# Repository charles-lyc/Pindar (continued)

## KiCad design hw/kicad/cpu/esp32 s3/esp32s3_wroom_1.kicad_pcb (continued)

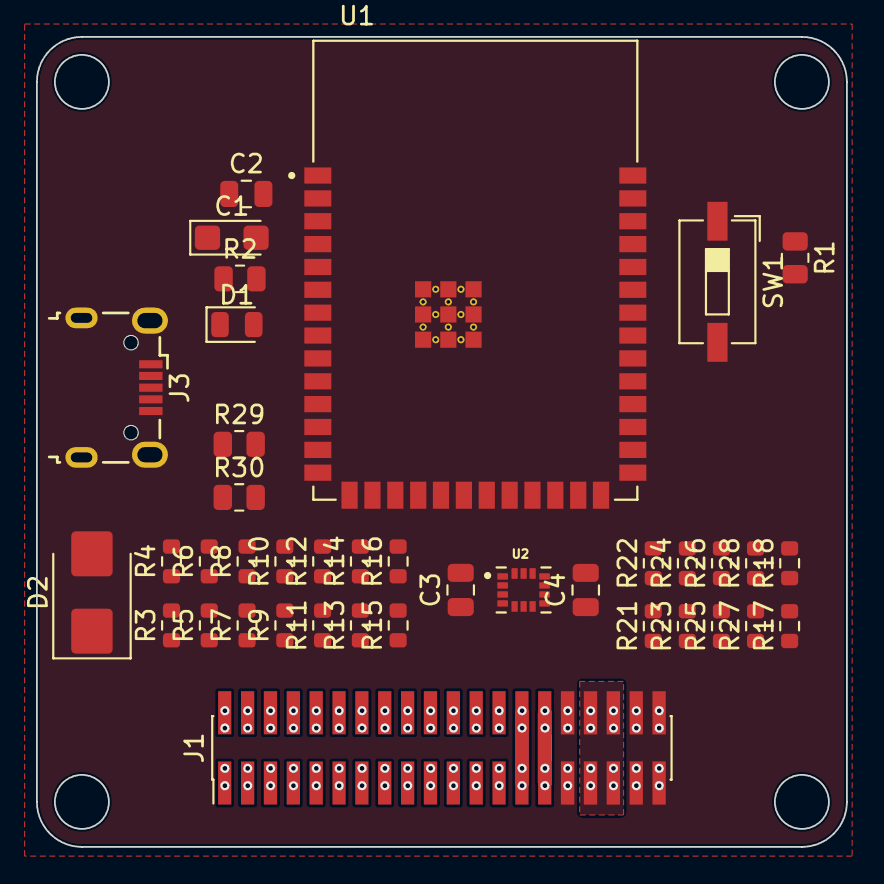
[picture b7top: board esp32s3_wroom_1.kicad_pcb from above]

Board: 2 copper layers, 45.0 x 45.0 mm, 40 parts (1 on the bottom side), 61 nets.

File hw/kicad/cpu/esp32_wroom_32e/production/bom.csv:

Designator,Footprint,Quantity,Value,LCSC Part #
C1,CP_EIA-7343-20_Kemet-V,1,200uF,
"C2, C3, C4",0603,3,0.1uF,
"J1, J2",PinHeader_2x20_P1.27mm_Vertical_SMD,2,Conn_02x20_Odd_Even,
"R1, R12, R13, R14, R15, R16, R17, R19, R2, R20, R21, R22, R23, R24, R25, R3, R4, R5, R6, R9",0603,20,100,
"R7, R8",0603,2,2k,
U1,ESP32-WROOM-32,1,ESP32-WROOM-32,
U2,ICM-42688-P,1,ICM-42688-P,

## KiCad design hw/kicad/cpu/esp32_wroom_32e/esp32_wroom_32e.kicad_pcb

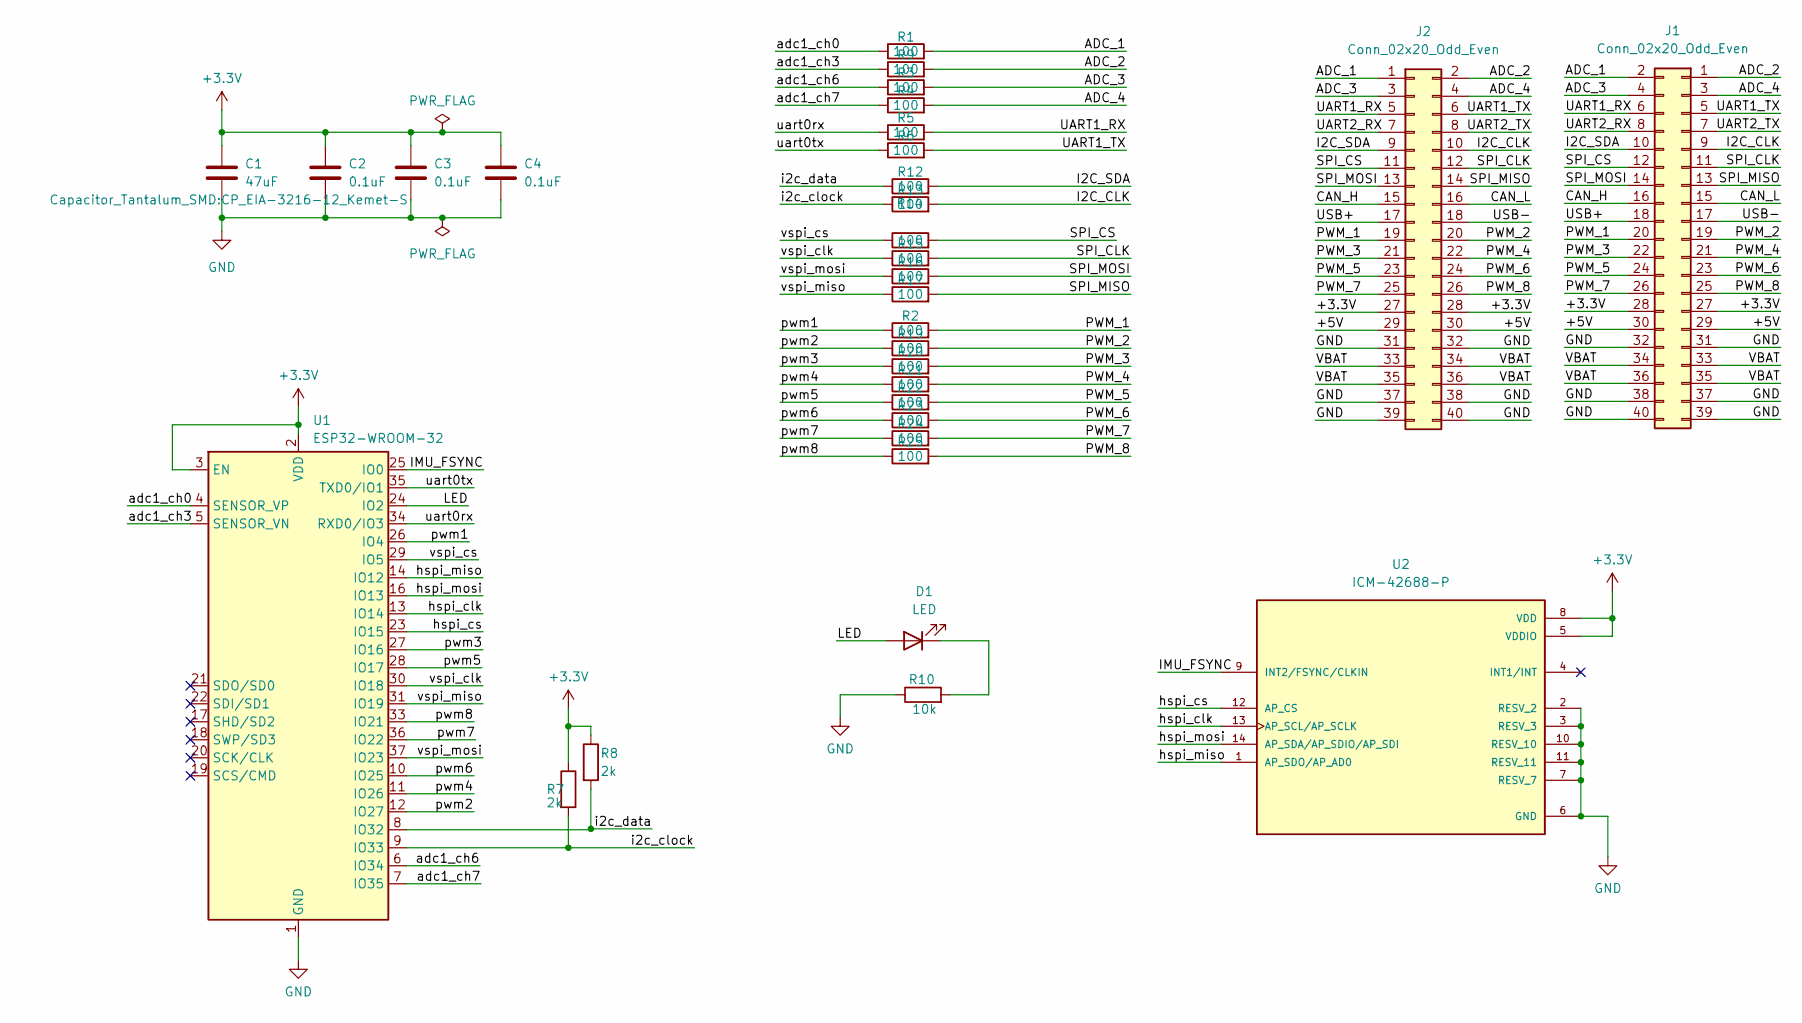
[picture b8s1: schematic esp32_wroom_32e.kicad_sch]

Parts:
C1: 47uF; CP_EIA-3216-12_Kemet-S
C2, C3, C4: 0.1uF; C_0805_2012Metric
D1: LED; LED_0805_2012Metric
J1, J2: Conn_02x20_Odd_Even; PinHeader_2x20_P1.27mm_Vertical_SMD
R1, R2, R3, R4, R5, R6, R9, R12, R13, R14, R15, R16, R17, R19, R20, R21, R22, R23, R24, R25: 100; R_0603_1608Metric
R7, R8: 2k; R_0805_2012Metric
R10: 10k; R_0805_2012Metric
U1: ESP32-WROOM-32
U2: ICM-42688-P; PARTREV 1.2

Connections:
+3.3V: C1.1, C2.1, C3.1, C4.1, J1.27, J1.28, J2.27, J2.28, R7.1, R8.1, U1.2 (VDD), U1.3 (EN), U2.5 (VDDIO), U2.8 (VDD)
/+5V: J1.29, J1.30, J2.29, J2.30
/ADC_1: J1.2, J2.1, R1.2
/ADC_2: J1.1, J2.2, R9.2
/ADC_3: J1.4, J2.3, R3.2
/ADC_4: J1.3, J2.4, R4.2
/CAN_H: J1.16, J2.15
/CAN_L: J1.15, J2.16
/I2C_CLK: J1.9, J2.10, R13.2
/I2C_SDA: J1.10, J2.9, R12.2
/IMU_FSYNC: U1.25 (IO0), U2.9 (INT2/FSYNC/CLKIN)
/LED: D1.2 (A), U1.24 (IO2)
/PWM_1: J1.20, J2.19, R2.2
/PWM_2: J1.19, J2.20, R19.2
/PWM_3: J1.22, J2.21, R20.2
/PWM_4: J1.21, J2.22, R21.2
/PWM_5: J1.24, J2.23, R22.2
/PWM_6: J1.23, J2.24, R23.2
/PWM_7: J1.26, J2.25, R24.2
/PWM_8: J1.25, J2.26, R25.2
/SPI_CLK: J1.11, J2.12, R15.2
/SPI_CS: J1.12, J2.11, R14.2
/SPI_MISO: J1.13, J2.14, R17.2
/SPI_MOSI: J1.14, J2.13, R16.2
/UART1_RX: J1.6, J2.5, R5.2
/UART1_TX: J1.5, J2.6, R6.2
/UART2_RX: J1.8, J2.7
/UART2_TX: J1.7, J2.8
/USB+: J1.18, J2.17
/USB-: J1.17, J2.18
/VBAT: J1.33, J1.34, J1.35, J1.36, J2.33, J2.34, J2.35, J2.36
/adc1_ch0: R1.1, U1.4 (SENSOR_VP)
/adc1_ch3: R9.1, U1.5 (SENSOR_VN)
/adc1_ch6: R3.1, U1.6 (IO34)
/adc1_ch7: R4.1, U1.7 (IO35)
/hspi_clk: U1.13 (IO14), U2.13 (AP_SCL/AP_SCLK)
/hspi_cs: U1.23 (IO15), U2.12 (AP_CS)
/hspi_miso: U1.14 (IO12), U2.1 (AP_SDO/AP_AD0)
/hspi_mosi: U1.16 (IO13), U2.14 (AP_SDA/AP_SDIO/AP_SDI)
/i2c_clock: R7.2, R13.1, U1.9 (IO33)
/i2c_data: R8.2, R12.1, U1.8 (IO32)
/pwm1: R2.1, U1.26 (IO4)
/pwm2: R19.1, U1.12 (IO27)
/pwm3: R20.1, U1.27 (IO16)
/pwm4: R21.1, U1.11 (IO26)
/pwm5: R22.1, U1.28 (IO17)
/pwm6: R23.1, U1.10 (IO25)
/pwm7: R24.1, U1.36 (IO22)
/pwm8: R25.1, U1.33 (IO21)
/uart0rx: R5.1, U1.34 (RXD0/IO3)
/uart0tx: R6.1, U1.35 (TXD0/IO1)
/vspi_clk: R15.1, U1.30 (IO18)
/vspi_cs: R14.1, U1.29 (IO5)
/vspi_miso: R17.1, U1.31 (IO19)
/vspi_mosi: R16.1, U1.37 (IO23)
GND: C1.2, C2.2, C3.2, C4.2, J1.31, J1.32, J1.37, J1.38, J1.39, J1.40, J2.31, J2.32, J2.37, J2.38, J2.39, J2.40, R10.1, U1.1 (GND), U1.15 (GND), U1.38 (GND), U1.39 (GND), U2.2 (RESV_2), U2.3 (RESV_3), U2.6 (GND), U2.7 (RESV_7), U2.10 (RESV_10), U2.11 (RESV_11)
unnamed: D1.1 (K), R10.2

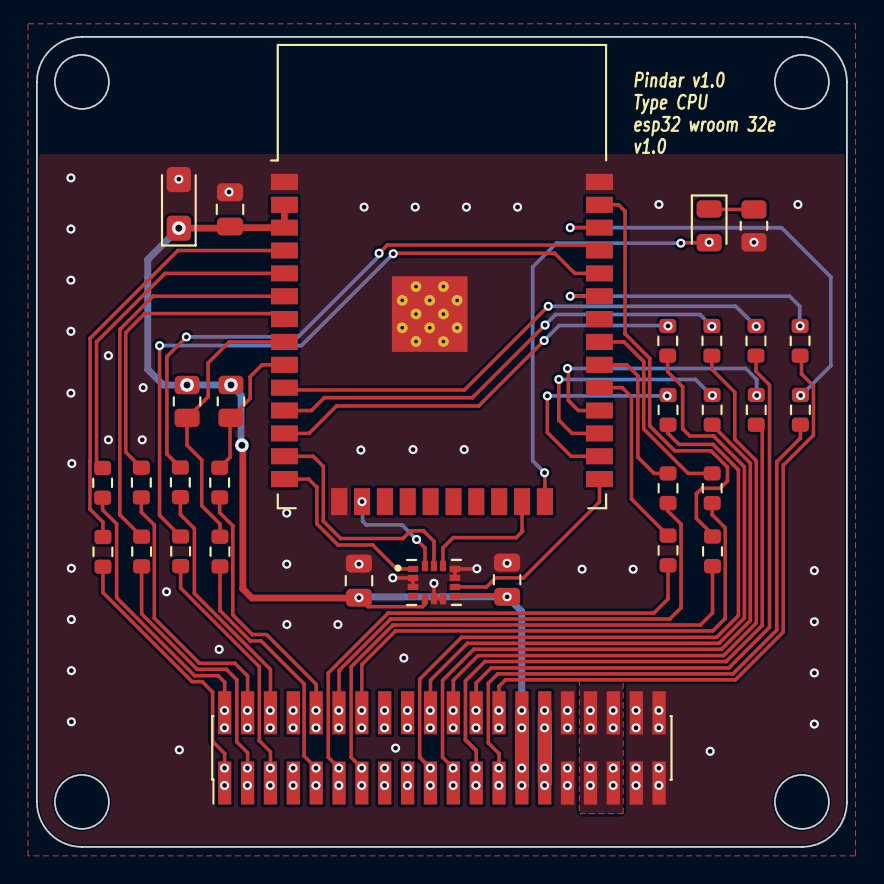
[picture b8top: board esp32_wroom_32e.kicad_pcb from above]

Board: 2 copper layers, 45.0 x 45.0 mm, 32 parts (1 on the bottom side), 57 nets.

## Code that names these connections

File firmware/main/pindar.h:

#pragma once

#include "freertos/FreeRTOS.h"
#include "freertos/task.h"
#include "freertos/semphr.h"

#include "mcu/spi.h"
#include "mcu/gpio_intr.h"

class Pindar {
public:
	// on board imu bus and gpio
	Pindar();
	~Pindar();

	// SerialPort *serial1= nullptr;
	// SerialPort *serial2= nullptr;

	SPI_Interface *spi2_bus = nullptr;
	SPI_Interface *spi3_bus = nullptr;
	// I2C_Interface *i2c_bus = nullptr;
	GPIO_Interrupt *gpio_imu = nullptr;

	// GPIO_Interface *gpio_1;
	// GPIO_Interface *gpio_2;
	// GPIO_Interface *gpio_3;
	// GPIO_Interface *gpio_4;
	// GPIO_Interface *gpio_5;
	// GPIO_Interface *gpio_6;
	// GPIO_Interface *gpio_7;
	// GPIO_Interface *gpio_8;
	// GPIO_Interface *gpio_9;
	// GPIO_Interface *gpio_10;
	// GPIO_Interface *gpio_11;
	// GPIO_Interface *gpio_12;
private:
};

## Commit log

2023-06-21 第一次打板，感觉可以再做小一点，并更新几个小问题。
2023-06-23 修改尺寸至45x45
2023-06-23 更新了template
2023-06-24 Pindar v1.0
2023-06-24 更新read me
2023-06-25 新增陀螺仪小板子
2023-06-29 第二次打样的整改；dc motor改成了三路 io不够做不了四路；
2023-06-29 修改名字
2023-06-30 更换接口线序
2023-07-01 更新app gyro板
2023-07-02 我又改接口了
2023-07-05 尽力改成40mmx40mm
2023-07-06 esp32部分该小板框可太难了，小电阻太多，只好全部去掉。
2023-07-06 原件位置
2023-07-08 cpu板io电阻
2023-07-08 增加电流传感器芯片
2023-07-13 更新dc motor板
2023-07-13 新增app板 PMW3360
2023-07-13 更新power16V板
2023-07-13 更新CPU板
2023-07-14 更新ESP32 S3 CPU板
2023-07-14 更新打样资料
2023-07-15 更新gyro
2023-07-23 更新power16v一些错误
2023-07-24 修改光流板一些错误
2023-07-30 更新USB micro 为优信的封装
2023-08-01 pindar平台接口的初步构想，但实际情况是，直接用esp32的API写几个器件驱动，后续照着这个模板来做即可，单独封一层显得多余。不过仍可以慢慢补充，当哪天接口覆盖面足够时就可以直接用pindar简化过的接口了。
2023-08-01 添加了io口定义，任何外设只要include了io定义+esp32的接口，就可以使用pindar bus上的资源了
2023-08-01 添加battery示例
2023-08-07 更新fw
2023-08-09 更新gitignore
2023-08-15 新增APP板 ADIS16460
2023-08-21 更新了代码框架
2023-08-22 更新IMU细节
2023-08-23 更新imu_scan_test
2023-08-23 fix编译
2023-08-26 new 任务打印功能
2023-08-27 update 文件结构
2023-08-28 fix compile
2023-08-28 remove build
2023-08-28 update ADC
2023-08-28 update app
2023-08-30 update py
2023-08-30 new serial
2023-08-30 update gpio
2023-08-30 fix 编译
2023-08-31 update motor
2023-09-03 update 部分驱动
2023-09-05 update 上位机
2023-09-06 fix spi
2024-08-05 add photos
